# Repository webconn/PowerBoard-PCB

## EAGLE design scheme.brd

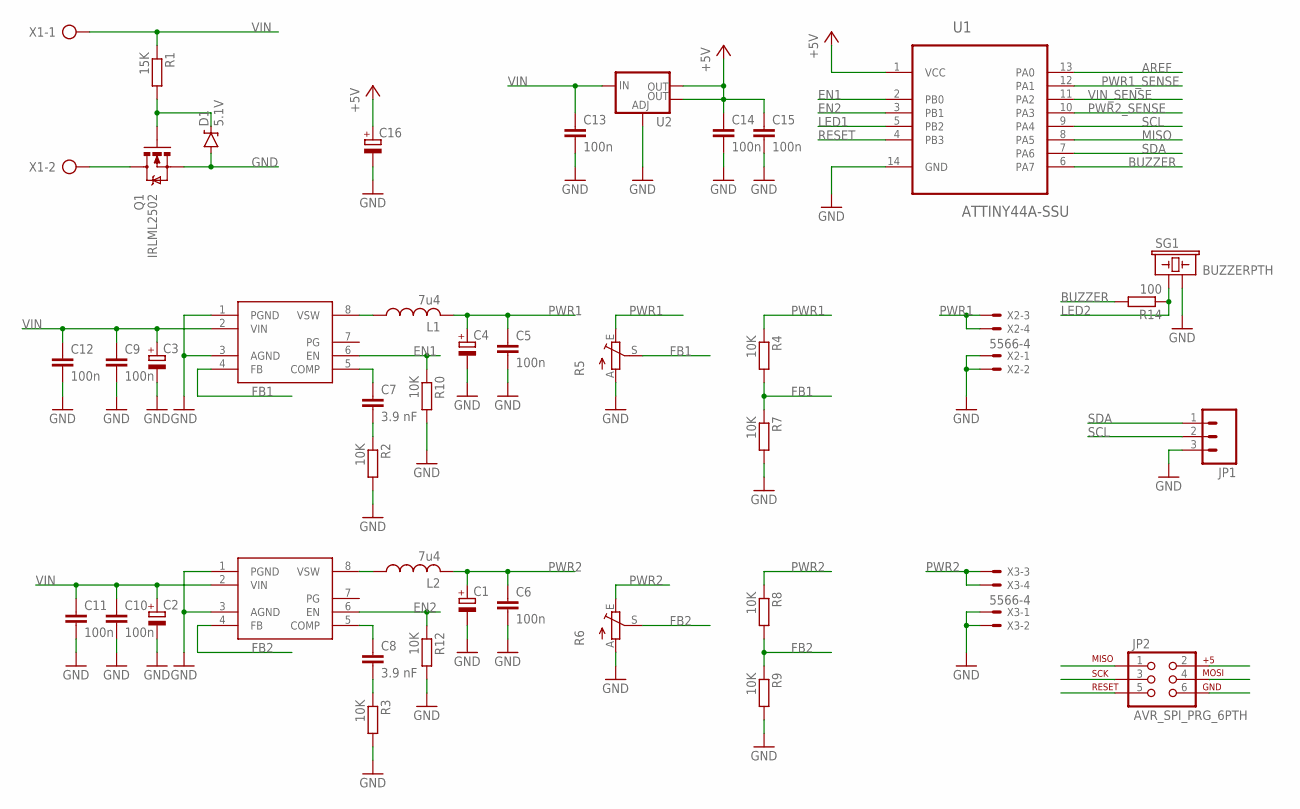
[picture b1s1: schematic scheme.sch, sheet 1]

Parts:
C1, C2, C3, C4, C16: CPOL-EUD/7343-31R; D/7343-31R
C5, C6, C9, C10, C11, C12, C13, C14, C15: 100n; C0805
C7, C8: 3.9 nF; C0805
D1: 5.1V; SOD-323
JP1: M03PTH; 1X03
JP2: AVR_SPI_PRG_6PTH; 2X3
L1, L2: 7u4; CDRH6D38
Q1: IRLML2502; SOT23-3
R1: 15K; R0805
R2, R3, R4, R7, R8, R9, R10, R12: 10K; R0805
R5, R6: TRIM_EU-RJ9W; RJ9W
R14: 100; R0805
SG1: BUZZERPTH; BUZZER-12MM
U1: ATTINY44A-SSU; SOIC127P600X175-14N
U2: V_REG_LM1117SOT223; SOT223
U$1, U$2: NCP3170; SO08
X1: AK500/2
X2, X3: 5566-4

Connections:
+5V: C14.1, C15.1, C16.+, JP2.2, U1.1 (VCC), U2.2 (OUT), U2.4 (OUT); also elsewhere on the board
AREF: U1.13 (PA0); also elsewhere on the board
BUZZER: R14.2, U1.6 (PA7)
EN1: R10.1, U1.2 (PB0), U$2.6 (EN)
EN2: R12.1, U1.3 (PB1), U$1.6 (EN)
FB1: R4.2, R5.S, R7.1, U$2.4 (FB)
FB2: R6.S, R8.2, R9.1, U$1.4 (FB)
GND: C1.-, C2.-, C3.-, C4.-, C5.2, C6.2, C9.2, C10.2, C11.2, C12.2, C13.2, C14.2, C15.2, C16.-, D1.A, JP1.3, JP2.6, Q1.2 (S), R2.2, R3.2, R5.A, R6.A, R7.2, R9.2, R10.2, R12.2, SG1.- (2), U1.14 (GND), U2.1 (ADJ), U$1.1 (PGND), U$1.3 (AGND), U$2.1 (PGND), U$2.3 (AGND), X2.1, X2.2, X3.1, X3.2; also elsewhere on the board
LED1: U1.5 (PB2); also elsewhere on the board
LED2: R14.1, SG1.+ (1); also elsewhere on the board
MISO: JP2.1, U1.8 (PA5); also elsewhere on the board
unnamed: Q1.3 (D), X1.2
unnamed: L1.1, U$2.8 (VSW)
unnamed: D1.C, Q1.1 (G), R1.2
unnamed: L2.1, U$1.8 (VSW)
unnamed: C7.1, U$2.5 (COMP)
unnamed: C8.1, U$1.5 (COMP)
unnamed: C7.2, R2.1
unnamed: C8.2, R3.1
PWR1: C4.+, C5.1, L1.2, R4.1, R5.E, X2.3, X2.4; also elsewhere on the board
PWR1_SENSE: U1.12 (PA1); also elsewhere on the board
PWR2: C1.+, C6.1, L2.2, R6.E, R8.1, X3.3, X3.4; also elsewhere on the board
PWR2_SENSE: U1.10 (PA3); also elsewhere on the board
RESET: JP2.5, U1.4 (PB3)
SCL: JP1.2, JP2.3, U1.9 (PA4)
SDA: JP1.1, JP2.4, U1.7 (PA6)
VIN: C2.+, C3.+, C9.1, C10.1, C11.1, C12.1, C13.1, R1.1, U2.3 (IN), U$1.2 (VIN), U$2.2 (VIN), X1.1; also elsewhere on the board
VIN_SENSE: U1.11 (PA2); also elsewhere on the board

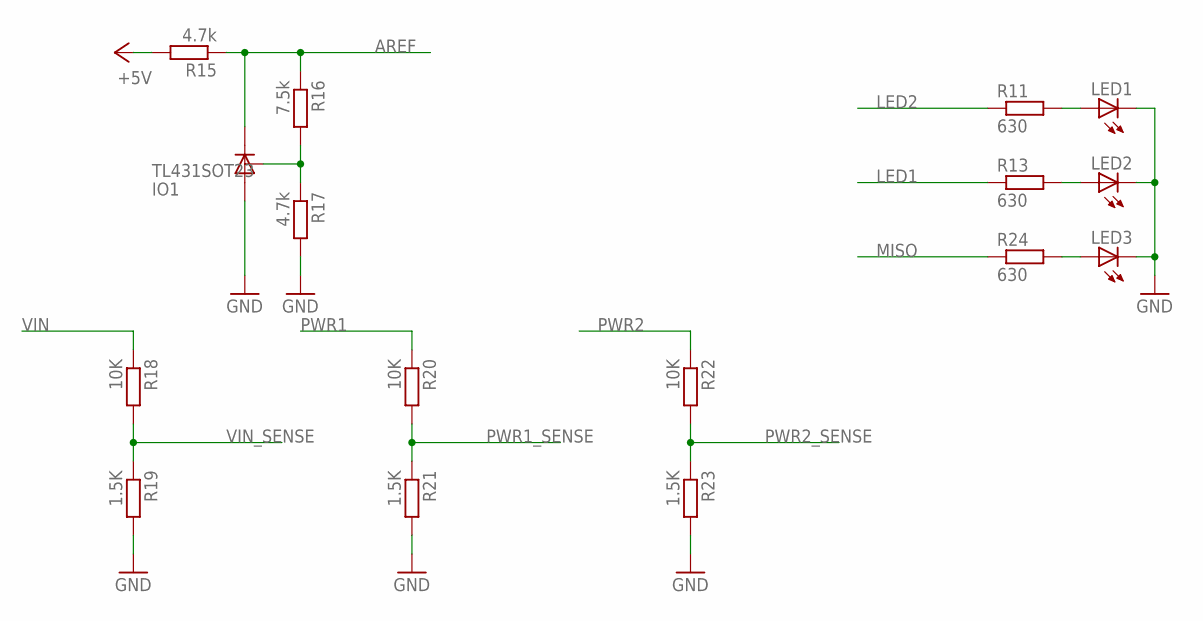
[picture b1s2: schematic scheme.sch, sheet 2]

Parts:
IO1: TL431SOT23; SOT23
LED1, LED2, LED3: LEDCHIPLED_0805; CHIPLED_0805
R11, R13, R24: 630; R0805
R15, R17: 4.7k; R0805
R16: 7.5k; R0805
R18, R20, R22: 10K; R0805
R19, R21, R23: 1.5K; R0805

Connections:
+5V: R15.2; also elsewhere on the board
AREF: IO1.1 (C), R15.1, R16.1; also elsewhere on the board
GND: IO1.3 (A), LED1.C, LED2.C, LED3.C, R17.2, R19.2, R21.2, R23.2; also elsewhere on the board
LED1: R13.1; also elsewhere on the board
LED2: R11.1; also elsewhere on the board
MISO: R24.1; also elsewhere on the board
unnamed: LED1.A, R11.2
unnamed: IO1.2 (R), R16.2, R17.1
unnamed: LED2.A, R13.2
unnamed: LED3.A, R24.2
PWR1: R20.1; also elsewhere on the board
PWR1_SENSE: R20.2, R21.1; also elsewhere on the board
PWR2: R22.1; also elsewhere on the board
PWR2_SENSE: R22.2, R23.1; also elsewhere on the board
VIN: R18.1; also elsewhere on the board
VIN_SENSE: R18.2, R19.1; also elsewhere on the board

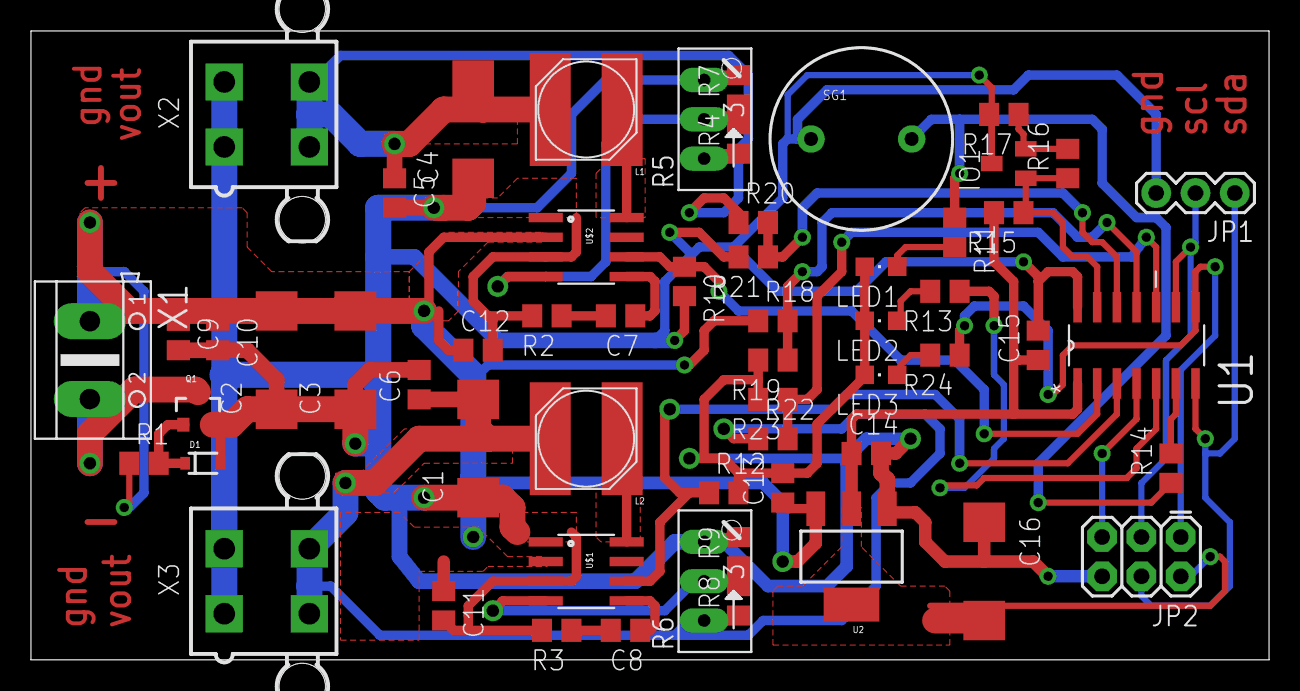
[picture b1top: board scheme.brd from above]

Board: 2 copper layers, 80.0 x 40.6 mm, 58 parts (0 on the bottom side), 32 nets.

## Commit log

2016-03-17 Fix isolate on left botton GND
2016-03-17 Add gitignore

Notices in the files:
parts and their libraries:
SparkFun-DiscreteSemi: Licensing: Creative Commons ShareAlike 4.0 International - https://creativecommons.org/licenses/by-sa/4.0
